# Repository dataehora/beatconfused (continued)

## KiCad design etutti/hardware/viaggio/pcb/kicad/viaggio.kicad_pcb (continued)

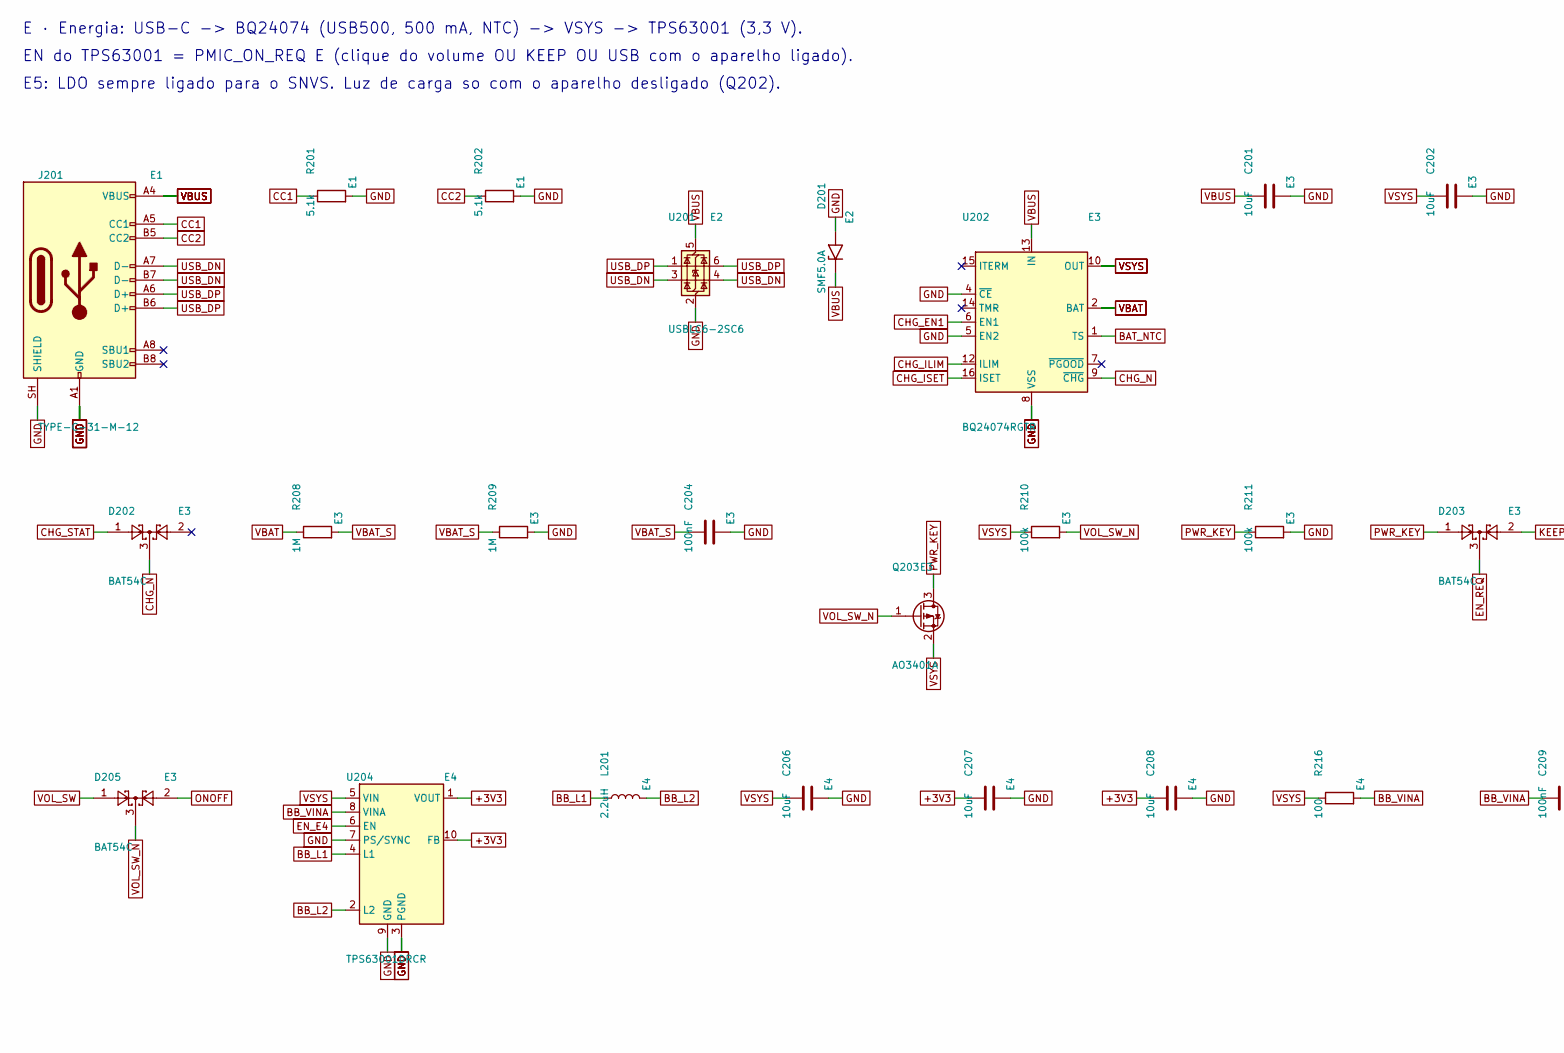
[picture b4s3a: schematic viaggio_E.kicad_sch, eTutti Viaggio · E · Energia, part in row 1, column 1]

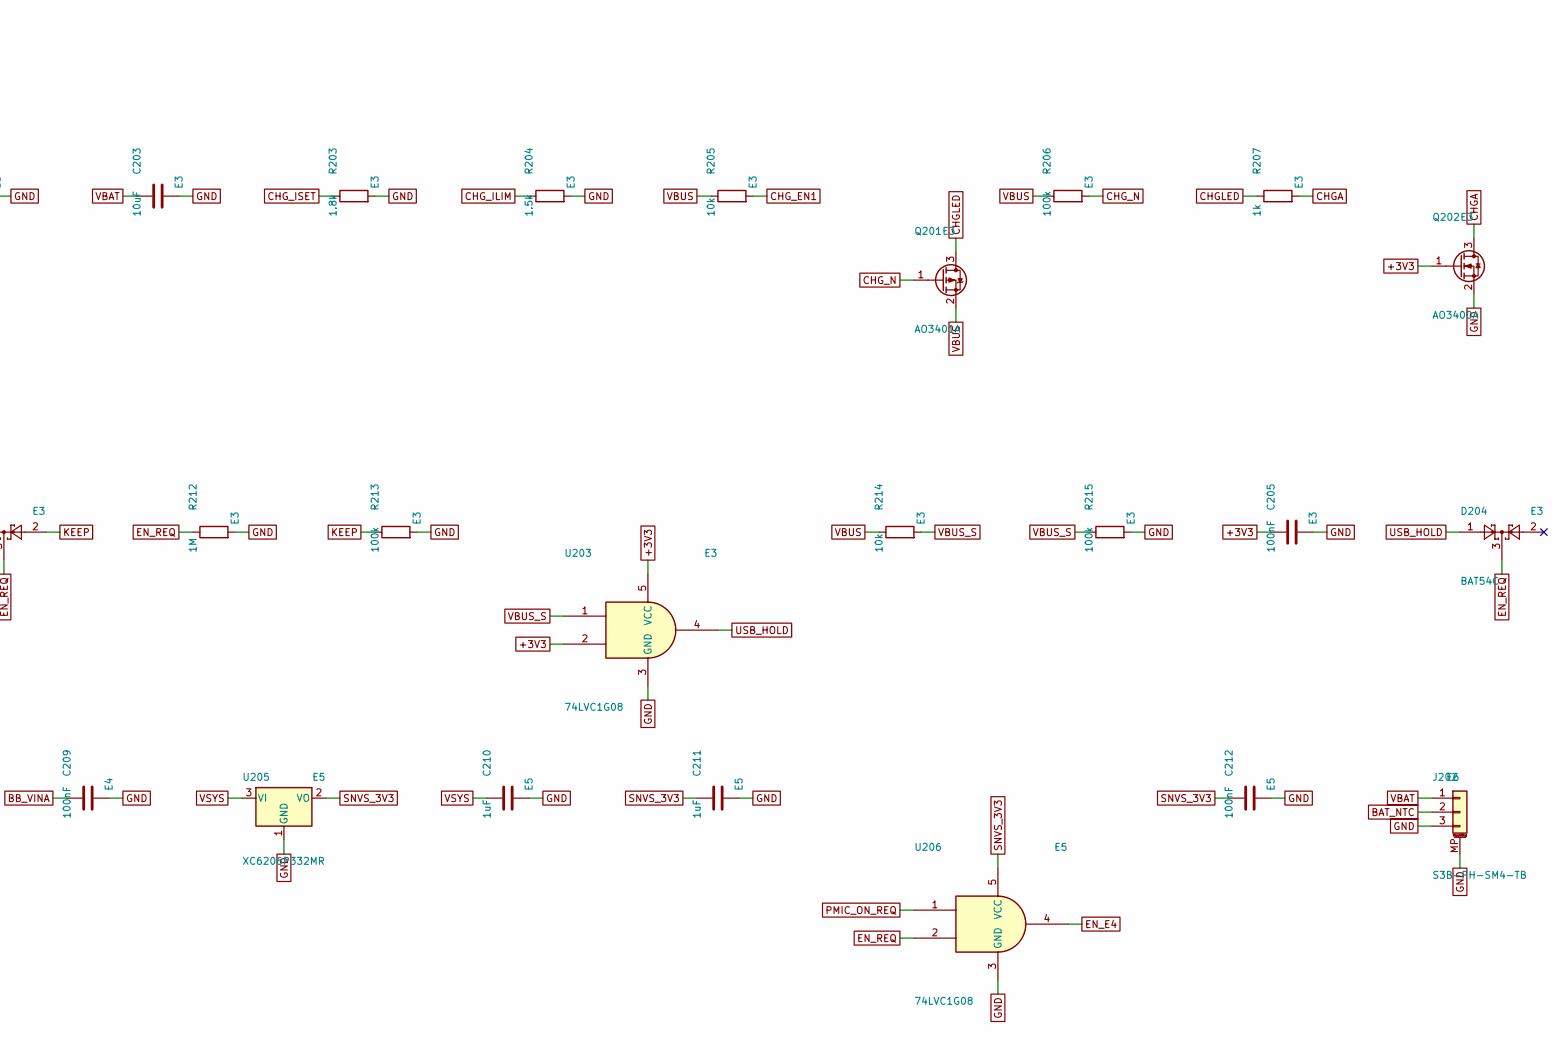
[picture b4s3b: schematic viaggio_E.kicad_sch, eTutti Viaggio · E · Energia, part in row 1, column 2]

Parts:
C201, C202, C203, C206, C207, C208: 10uF; C_0805_2012Metric; LCSC C15850
C204, C205, C209, C212: 100nF; C_0402_1005Metric; LCSC C1525
C210, C211: 1uF; C_0402_1005Metric; LCSC C52923
D201: SMF5.0A; D_SOD-123F; LCSC C151296
D202, D203, D204, D205: BAT54C; SOT-23; LCSC C134405
J201: TYPE-C-31-M-12; USB_C_Receptacle_HRO_TYPE-C-31-M-12; LCSC C165948
J202: S3B-PH-SM4-TB; JST_PH_S3B-PH-SM4-TB_1x03-1MP_P2.00mm_Horizontal; LCSC C265101
L201: 2.2uH; L_Changjiang_FNR4020S; LCSC C167825
Q201, Q203: AO3401A; SOT-23; LCSC C15127
Q202: AO3400A; SOT-23; LCSC C20917
R201, R202: 5.1k; R_0402_1005Metric; LCSC C25905
R203: 1.8k; R_0402_1005Metric; LCSC C25811
R204: 1.5k; R_0402_1005Metric; LCSC C25867
R205, R214: 10k; R_0402_1005Metric; LCSC C25744
R206, R210, R211, R213, R215: 100k; R_0402_1005Metric; LCSC C25741
R207: 1k; R_0402_1005Metric; LCSC C11702
R208, R209, R212: 1M; R_0402_1005Metric; LCSC C26083
R216: 100; R_0402_1005Metric; LCSC C25076
U201: USBLC6-2SC6; SOT-23-6; LCSC C7519
U202: BQ24074RGTR; VQFN-16-1EP_3x3mm_P0.5mm_EP1.6x1.6mm; LCSC C54313
U203, U206: 74LVC1G08; SOT-23-5; LCSC C7666
U204: TPS63001DRCR; Texas_DRC0010J; LCSC C28060
U205: XC6206P332MR; SOT-23-3; LCSC C5446

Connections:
+3V3: C205.1, C207.1, C208.1, Q202.1 (G), U203.2, U203.5 (VCC), U204.1 (VOUT), U204.10 (FB); also elsewhere on the board
BAT_NTC: J202.2, U202.1 (TS)
BB_L1: L201.1, U204.4 (L1)
BB_L2: L201.2, U204.2 (L2)
BB_VINA: C209.1, R216.2, U204.8 (VINA)
CC1: J201.A5 (CC1), R201.1
CC2: J201.B5 (CC2), R202.1
CHGA: Q202.3 (D), R207.2; also elsewhere on the board
CHGLED: Q201.3 (D), R207.1
CHG_EN1: R205.2, U202.6 (EN1)
CHG_ILIM: R204.1, U202.12 (ILIM)
CHG_ISET: R203.1, U202.16 (ISET)
CHG_N: D202.3, Q201.1 (G), R206.2, U202.9 (~CHG)
CHG_STAT: D202.1; also elsewhere on the board
EN_E4: U204.6 (EN), U206.4
EN_REQ: D203.3, D204.3, R212.1, U206.2
GND: C201.2, C202.2, C203.2, C204.2, C205.2, C206.2, C207.2, C208.2, C209.2, C210.2, C211.2, C212.2, D201.2 (A2), J201.A1 (GND), J201.A12 (GND), J201.B1 (GND), J201.B12 (GND), J201.SH (SHIELD), J202.3, J202.MP (MountPin), Q202.2 (S), R201.2, R202.2, R203.2, R204.2, R209.2, R211.2, R212.2, R213.2, R215.2, U201.2 (GND), U202.4 (~CE), U202.5 (EN2), U202.8 (VSS), U202.17 (VSS), U203.3 (GND), U204.3 (PGND), U204.7 (PS/SYNC), U204.9 (GND), U204.11 (PGND), U205.1 (GND), U206.3 (GND); also elsewhere on the board
KEEP: D203.2, R213.1; also elsewhere on the board
ONOFF: D205.2; also elsewhere on the board
PMIC_ON_REQ: U206.1; also elsewhere on the board
PWR_KEY: D203.1, Q203.3 (D), R211.1
SNVS_3V3: C211.1, C212.1, U205.2 (VO), U206.5 (VCC); also elsewhere on the board
USB_DN: J201.A7 (D-), J201.B7 (D-), U201.3 (I/O2), U201.4 (I/O2); also elsewhere on the board
USB_DP: J201.A6 (D+), J201.B6 (D+), U201.1 (I/O1), U201.6 (I/O1); also elsewhere on the board
USB_HOLD: D204.1, U203.4
VBAT: C203.1, J202.1, R208.1, U202.2 (BAT), U202.3 (BAT)
VBAT_S: C204.1, R208.2, R209.1; also elsewhere on the board
VBUS: C201.1, D201.1 (A1), J201.A4 (VBUS), J201.A9 (VBUS), J201.B4 (VBUS), J201.B9 (VBUS), Q201.2 (S), R205.1, R206.1, R214.1, U201.5 (VBUS), U202.13 (IN); also elsewhere on the board
VBUS_S: R214.2, R215.1, U203.1
VOL_SW: D205.1; also elsewhere on the board
VOL_SW_N: D205.3, Q203.1 (G), R210.2; also elsewhere on the board
VSYS: C202.1, C206.1, C210.1, Q203.2 (S), R210.1, R216.1, U202.10 (OUT), U202.11 (OUT), U204.5 (VIN), U205.3 (VI); also elsewhere on the board

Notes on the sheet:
E · Energia: USB-C -> BQ24074 (USB500, 500 mA, NTC) -> VSYS -> TPS63001 (3,3 V).
EN do TPS63001 = PMIC_ON_REQ E (clique do volume OU KEEP OU USB com o aparelho ligado).
E5: LDO sempre ligado para o SNVS. Luz de carga so com o aparelho desligado (Q202).

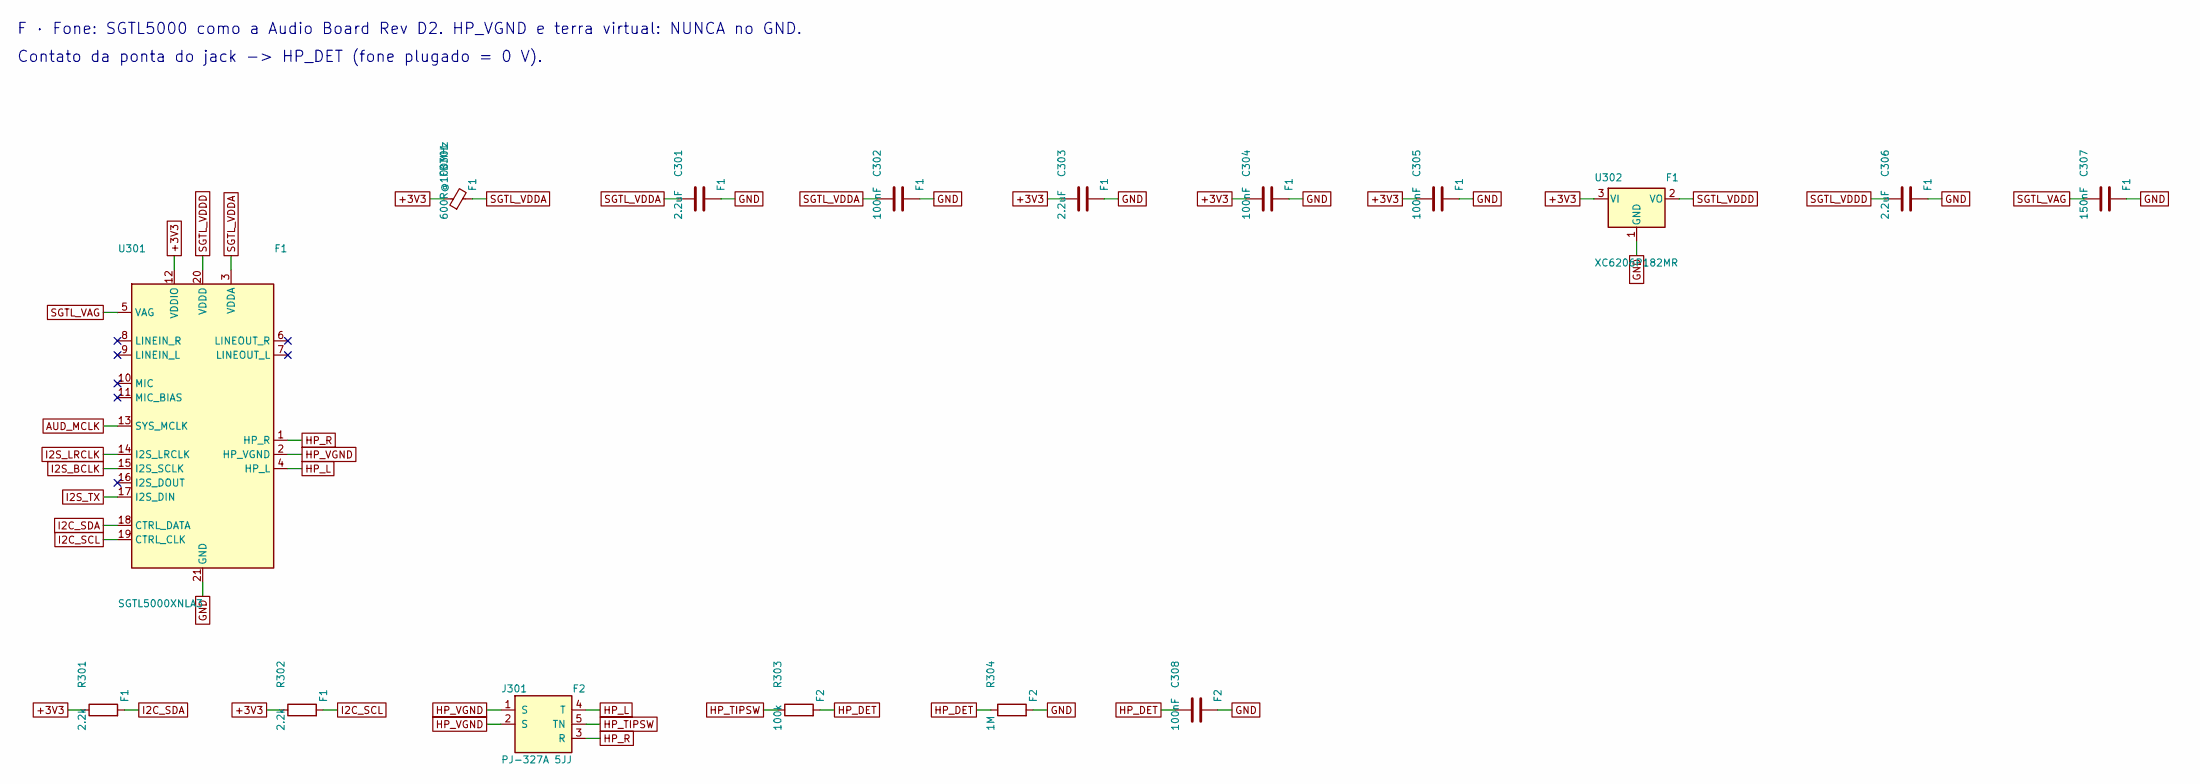
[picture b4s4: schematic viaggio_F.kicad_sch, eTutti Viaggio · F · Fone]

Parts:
C301, C303, C306: 2.2uF; C_0402_1005Metric; LCSC C12530
C302, C304, C305, C308: 100nF; C_0402_1005Metric; LCSC C1525
C307: 150nF; C_0402_1005Metric
FB301: 600R@100MHz; L_0603_1608Metric
J301: PJ-327A 5JJ; Jack_3.5mm_PJ-327A_SMD; LCSC C668605
R301, R302: 2.2k; R_0402_1005Metric; LCSC C25879
R303: 100k; R_0402_1005Metric; LCSC C25741
R304: 1M; R_0402_1005Metric; LCSC C26083
U301: SGTL5000XNLA3; QFN-20-1EP_3x3mm_P0.4mm_EP1.65x1.65mm; LCSC C511764
U302: XC6206P182MR; SOT-23-3; LCSC C347373

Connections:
+3V3: C303.1, C304.1, C305.1, FB301.1, R301.1, R302.1, U301.12 (VDDIO), U302.3 (VI); also elsewhere on the board
AUD_MCLK: U301.13 (SYS_MCLK); also elsewhere on the board
GND: C301.2, C302.2, C303.2, C304.2, C305.2, C306.2, C307.2, C308.2, R304.2, U301.21 (GND), U302.1 (GND); also elsewhere on the board
HP_DET: C308.1, R303.2, R304.1; also elsewhere on the board
HP_L: J301.4 (T), U301.4 (HP_L)
HP_R: J301.3 (R), U301.1 (HP_R)
HP_TIPSW: J301.5 (TN), R303.1
HP_VGND: J301.1 (S), J301.2 (S), U301.2 (HP_VGND)
I2C_SCL: R302.2, U301.19 (CTRL_CLK); also elsewhere on the board
I2C_SDA: R301.2, U301.18 (CTRL_DATA); also elsewhere on the board
I2S_BCLK: U301.15 (I2S_SCLK); also elsewhere on the board
I2S_LRCLK: U301.14 (I2S_LRCLK); also elsewhere on the board
I2S_TX: U301.17 (I2S_DIN); also elsewhere on the board
SGTL_VAG: C307.1, U301.5 (VAG)
SGTL_VDDA: C301.1, C302.1, FB301.2, U301.3 (VDDA)
SGTL_VDDD: C306.1, U301.20 (VDDD), U302.2 (VO)

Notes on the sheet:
F · Fone: SGTL5000 como a Audio Board Rev D2. HP_VGND e terra virtual: NUNCA no GND.
Contato da ponta do jack -> HP_DET (fone plugado = 0 V).

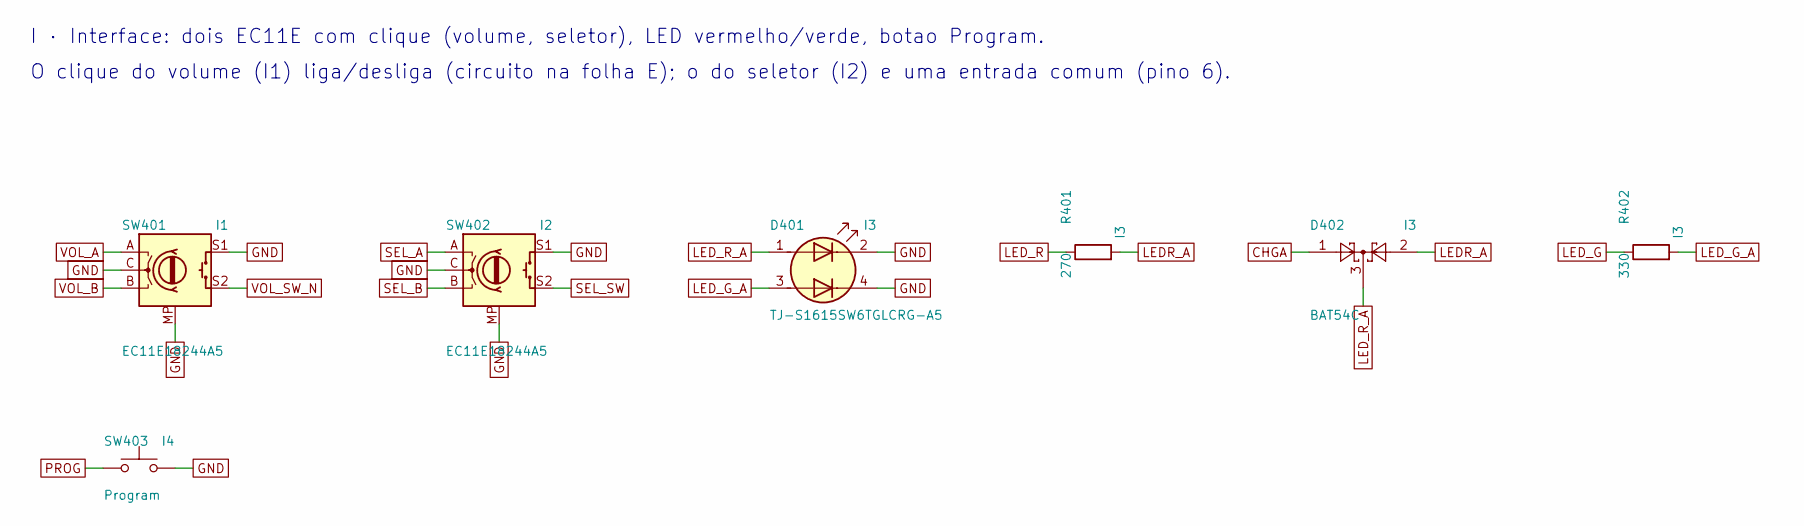
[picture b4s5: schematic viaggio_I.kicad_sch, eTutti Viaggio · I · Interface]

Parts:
D401: TJ-S1615SW6TGLCRG-A5; LED_1615_RG_4pad; LCSC C273605
D402: BAT54C; SOT-23; LCSC C134405
R401: 270; R_0402_1005Metric; LCSC C25190
R402: 330; R_0402_1005Metric; LCSC C25104
SW401, SW402: EC11E18244A5; RotaryEncoder_Alps_EC11E-Switch_Vertical_H20mm; LCSC C255515
SW403: Program; SW_Push_1P1T_XKB_TS-1187A; LCSC C318884

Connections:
CHGA: D402.1; also elsewhere on the board
GND: D401.2 (K1), D401.4 (K2), SW401.C, SW401.MP, SW401.S1, SW402.C, SW402.MP, SW402.S1, SW403.2; also elsewhere on the board
LEDR_A: D402.2, R401.2
LED_G: R402.1; also elsewhere on the board
LED_G_A: D401.3 (A2), R402.2
LED_R: R401.1; also elsewhere on the board
LED_R_A: D401.1 (A1), D402.3
PROG: SW403.1; also elsewhere on the board
SEL_A: SW402.A; also elsewhere on the board
SEL_B: SW402.B; also elsewhere on the board
SEL_SW: SW402.S2; also elsewhere on the board
VOL_A: SW401.A; also elsewhere on the board
VOL_B: SW401.B; also elsewhere on the board
VOL_SW_N: SW401.S2; also elsewhere on the board

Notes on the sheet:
I · Interface: dois EC11E com clique (volume, seletor), LED vermelho/verde, botao Program.
O clique do volume (I1) liga/desliga (circuito na folha E); o do seletor (I2) e uma entrada comum (pino 6).

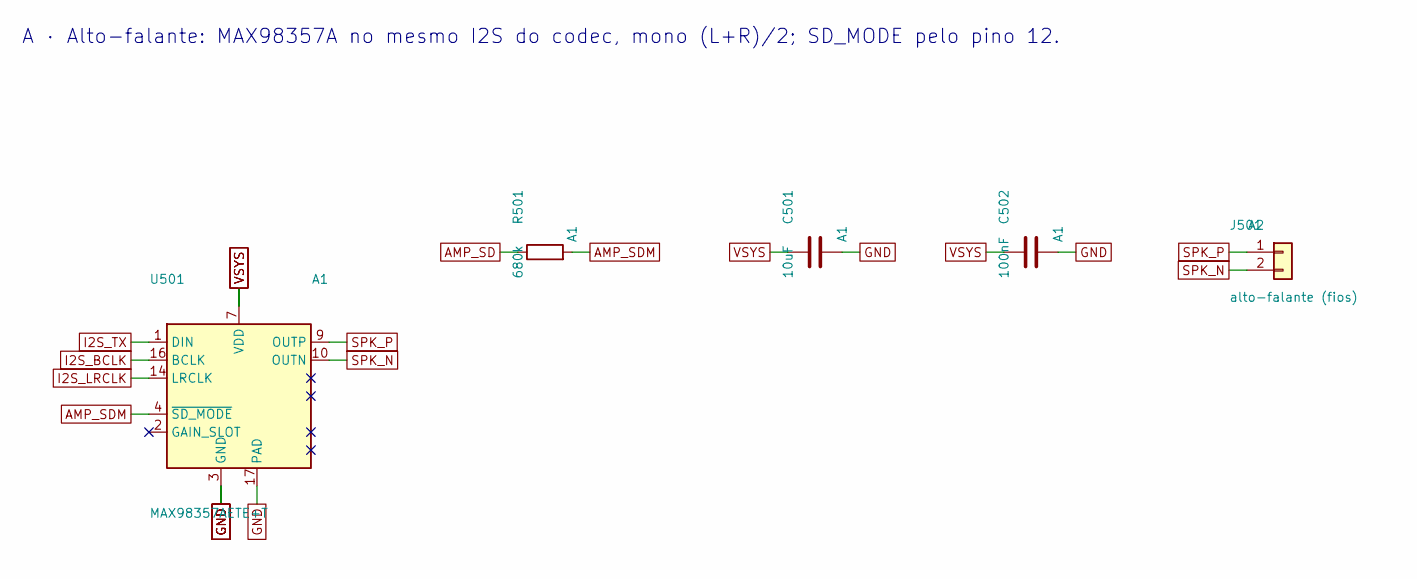
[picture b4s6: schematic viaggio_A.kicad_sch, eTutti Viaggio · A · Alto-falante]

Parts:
C501: 10uF; C_0805_2012Metric; LCSC C15850
C502: 100nF; C_0402_1005Metric; LCSC C1525
J501: alto-falante (fios); SolderWire-0.127sqmm_1x02_P3.7mm_D0.48mm_OD1mm
R501: 680k; R_0402_1005Metric
U501: MAX98357AETE+T; TQFN-16-1EP_3x3mm_P0.5mm_EP1.23x1.23mm; LCSC C910544

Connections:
AMP_SD: R501.1; also elsewhere on the board
AMP_SDM: R501.2, U501.4 (~SD_MODE)
GND: C501.2, C502.2, U501.3 (GND), U501.11 (GND), U501.15 (GND), U501.17 (PAD); also elsewhere on the board
I2S_BCLK: U501.16 (BCLK); also elsewhere on the board
I2S_LRCLK: U501.14 (LRCLK); also elsewhere on the board
I2S_TX: U501.1 (DIN); also elsewhere on the board
SPK_N: J501.2, U501.10 (OUTN)
SPK_P: J501.1, U501.9 (OUTP)
VSYS: C501.1, C502.1, U501.7 (VDD), U501.8 (VDD); also elsewhere on the board

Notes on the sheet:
A · Alto-falante: MAX98357A no mesmo I2S do codec, mono (L+R)/2; SD_MODE pelo pino 12.

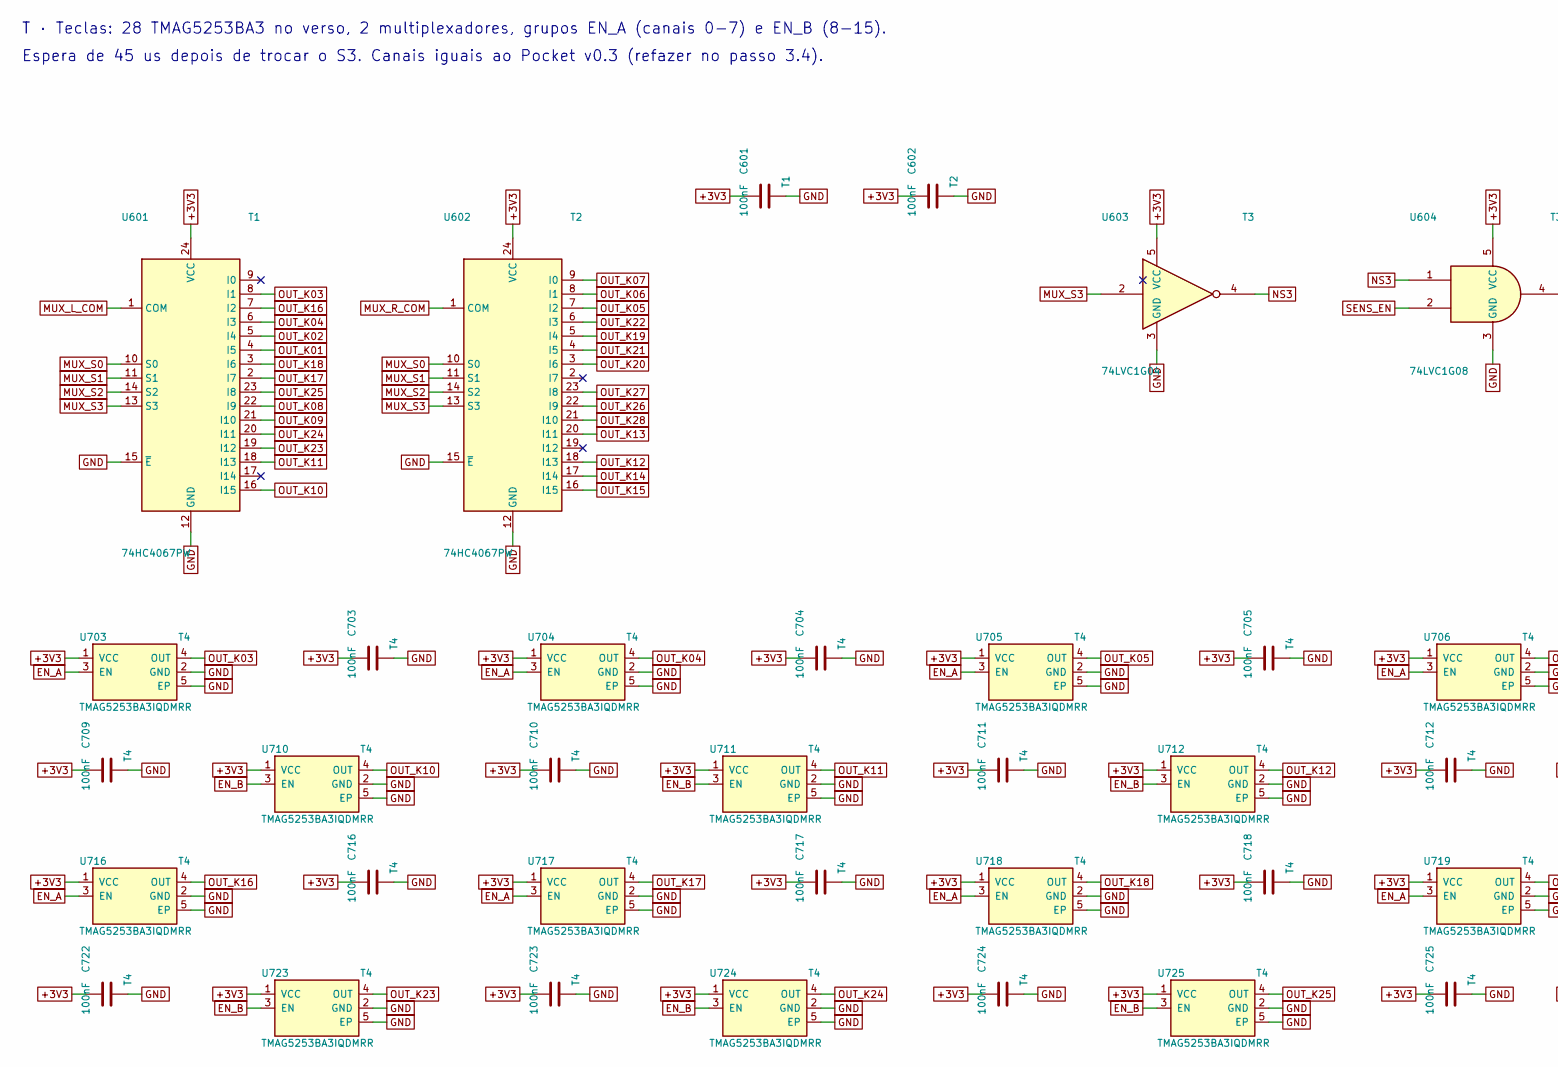
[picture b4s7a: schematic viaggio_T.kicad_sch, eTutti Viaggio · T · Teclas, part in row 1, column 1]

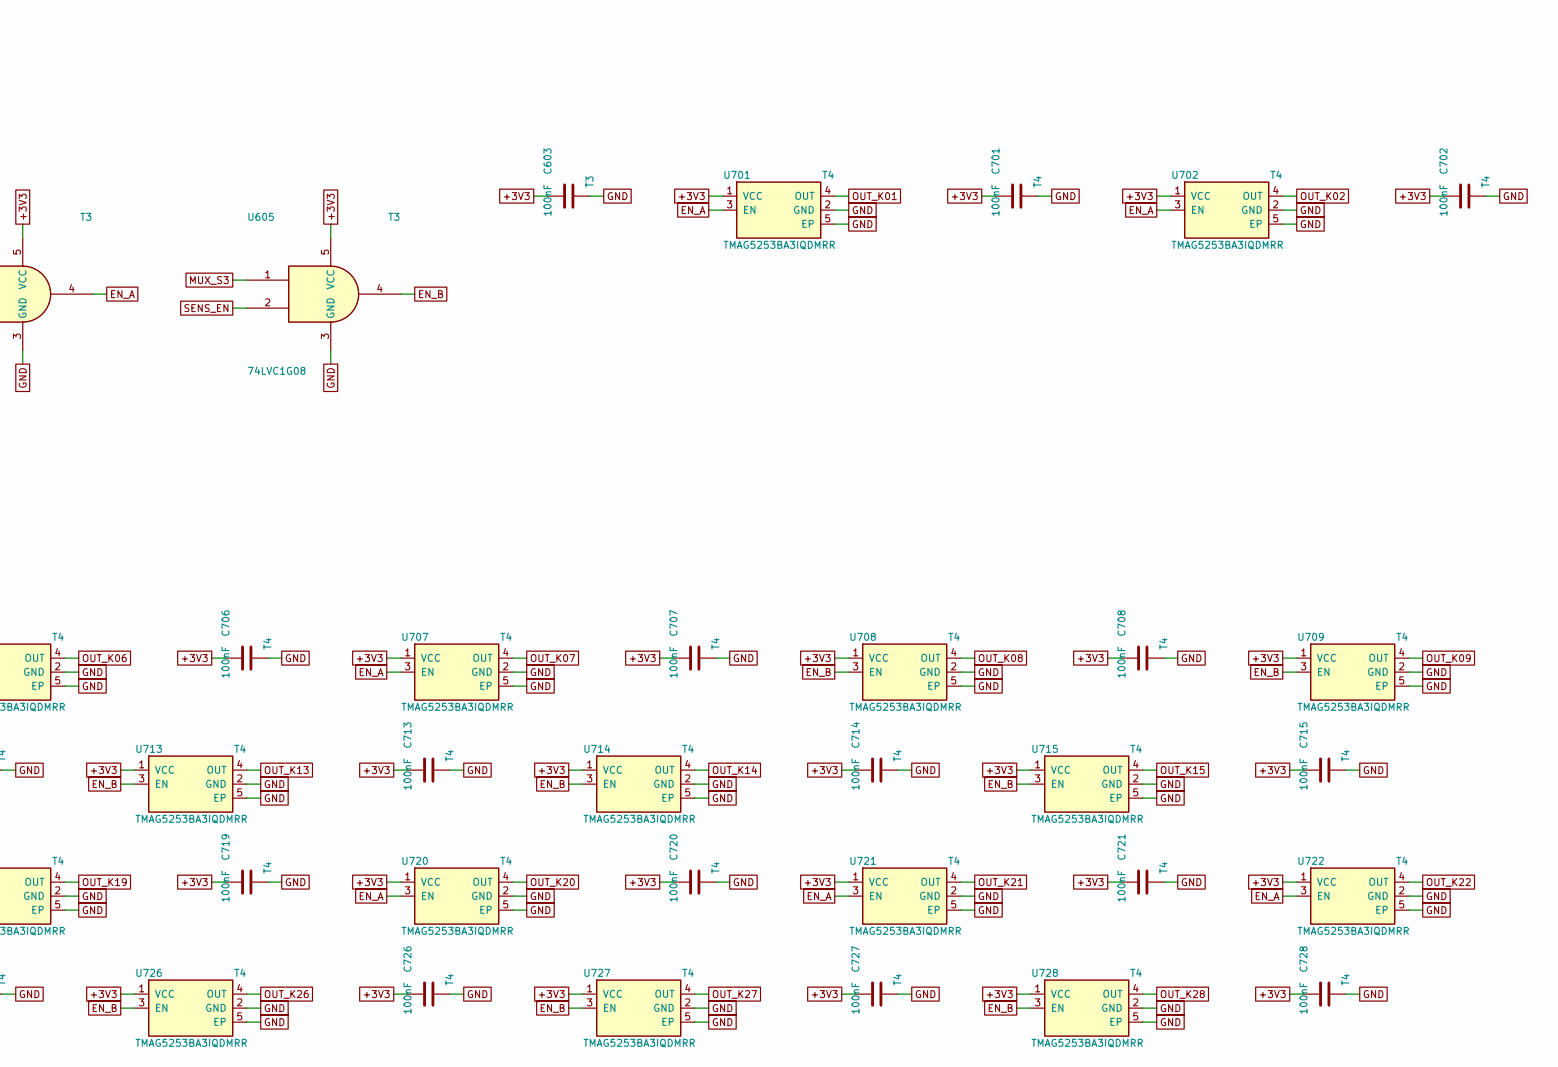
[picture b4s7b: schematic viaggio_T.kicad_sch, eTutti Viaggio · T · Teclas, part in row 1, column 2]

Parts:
C601, C602, C603, C701, C702, C703, C704, C705, C706, C707, C708, C709, C710, C711, C712, C713, C714, C715, C716, C717, C718, C719, C720, C721, C722, C723, C724, C725, C726, C727, C728: 100nF; C_0402_1005Metric; LCSC C1525
U601, U602: 74HC4067PW; TSSOP-24_4.4x7.8mm_P0.65mm; LCSC C547038
U603: 74LVC1G04; SOT-23-5; LCSC C7827
U604, U605: 74LVC1G08; SOT-23-5; LCSC C7666
U701, U702, U703, U704, U705, U706, U707, U708, U709, U710, U711, U712, U713, U714, U715, U716, U717, U718, U719, U720, U721, U722, U723, U724, U725, U726, U727, U728: TMAG5253BA3IQDMRR; Texas_X2SON-4-1EP_1.1x1.4mm_P0.5mm_EP0.8x0.6mm

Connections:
+3V3: C601.1, C602.1, C603.1, C701.1, C702.1, C703.1, C704.1, C705.1, C706.1, C707.1, C708.1, C709.1, C710.1, C711.1, C712.1, C713.1, C714.1, C715.1, C716.1, C717.1, C718.1, C719.1, C720.1, C721.1, C722.1, C723.1, C724.1, C725.1, C726.1, C727.1, C728.1, U601.24 (VCC), U602.24 (VCC), U603.5 (VCC), U604.5 (VCC), U605.5 (VCC), U701.1 (VCC), U702.1 (VCC), U703.1 (VCC), U704.1 (VCC), U705.1 (VCC), U706.1 (VCC), U707.1 (VCC), U708.1 (VCC), U709.1 (VCC), U710.1 (VCC), U711.1 (VCC), U712.1 (VCC), U713.1 (VCC), U714.1 (VCC), U715.1 (VCC), U716.1 (VCC), U717.1 (VCC), U718.1 (VCC), U719.1 (VCC), U720.1 (VCC), U721.1 (VCC), U722.1 (VCC), U723.1 (VCC), U724.1 (VCC), U725.1 (VCC), U726.1 (VCC), U727.1 (VCC), U728.1 (VCC); also elsewhere on the board
EN_A: U604.4, U701.3 (EN), U702.3 (EN), U703.3 (EN), U704.3 (EN), U705.3 (EN), U706.3 (EN), U707.3 (EN), U716.3 (EN), U717.3 (EN), U718.3 (EN), U719.3 (EN), U720.3 (EN), U721.3 (EN), U722.3 (EN)
EN_B: U605.4, U708.3 (EN), U709.3 (EN), U710.3 (EN), U711.3 (EN), U712.3 (EN), U713.3 (EN), U714.3 (EN), U715.3 (EN), U723.3 (EN), U724.3 (EN), U725.3 (EN), U726.3 (EN), U727.3 (EN), U728.3 (EN)
GND: C601.2, C602.2, C603.2, C701.2, C702.2, C703.2, C704.2, C705.2, C706.2, C707.2, C708.2, C709.2, C710.2, C711.2, C712.2, C713.2, C714.2, C715.2, C716.2, C717.2, C718.2, C719.2, C720.2, C721.2, C722.2, C723.2, C724.2, C725.2, C726.2, C727.2, C728.2, U601.12 (GND), U601.15 (~E), U602.12 (GND), U602.15 (~E), U603.3 (GND), U604.3 (GND), U605.3 (GND), U701.2 (GND), U701.5 (EP), U702.2 (GND), U702.5 (EP), U703.2 (GND), U703.5 (EP), U704.2 (GND), U704.5 (EP), U705.2 (GND), U705.5 (EP), U706.2 (GND), U706.5 (EP), U707.2 (GND), U707.5 (EP), U708.2 (GND), U708.5 (EP), U709.2 (GND), U709.5 (EP), U710.2 (GND), U710.5 (EP), U711.2 (GND), U711.5 (EP), U712.2 (GND), U712.5 (EP), U713.2 (GND), U713.5 (EP), U714.2 (GND), U714.5 (EP), U715.2 (GND), U715.5 (EP), U716.2 (GND), U716.5 (EP), U717.2 (GND), U717.5 (EP), U718.2 (GND), U718.5 (EP), U719.2 (GND), U719.5 (EP), U720.2 (GND), U720.5 (EP), U721.2 (GND), U721.5 (EP), U722.2 (GND), U722.5 (EP), U723.2 (GND), U723.5 (EP), U724.2 (GND), U724.5 (EP), U725.2 (GND), U725.5 (EP), U726.2 (GND), U726.5 (EP), U727.2 (GND), U727.5 (EP), U728.2 (GND), U728.5 (EP); also elsewhere on the board
MUX_L_COM: U601.1 (COM); also elsewhere on the board
MUX_R_COM: U602.1 (COM); also elsewhere on the board
MUX_S0: U601.10 (S0), U602.10 (S0); also elsewhere on the board
MUX_S1: U601.11 (S1), U602.11 (S1); also elsewhere on the board
MUX_S2: U601.14 (S2), U602.14 (S2); also elsewhere on the board
MUX_S3: U601.13 (S3), U602.13 (S3), U603.2, U605.1; also elsewhere on the board
NS3: U603.4, U604.1
OUT_K01: U601.4 (I5), U701.4 (OUT)
OUT_K02: U601.5 (I4), U702.4 (OUT)
OUT_K03: U601.8 (I1), U703.4 (OUT)
OUT_K04: U601.6 (I3), U704.4 (OUT)
OUT_K05: U602.7 (I2), U705.4 (OUT)
OUT_K06: U602.8 (I1), U706.4 (OUT)
OUT_K07: U602.9 (I0), U707.4 (OUT)
OUT_K08: U601.22 (I9), U708.4 (OUT)
OUT_K09: U601.21 (I10), U709.4 (OUT)
OUT_K10: U601.16 (I15), U710.4 (OUT)
OUT_K11: U601.18 (I13), U711.4 (OUT)
OUT_K12: U602.18 (I13), U712.4 (OUT)
OUT_K13: U602.20 (I11), U713.4 (OUT)
OUT_K14: U602.17 (I14), U714.4 (OUT)
OUT_K15: U602.16 (I15), U715.4 (OUT)
OUT_K16: U601.7 (I2), U716.4 (OUT)
OUT_K17: U601.2 (I7), U717.4 (OUT)
OUT_K18: U601.3 (I6), U718.4 (OUT)
OUT_K19: U602.5 (I4), U719.4 (OUT)
OUT_K20: U602.3 (I6), U720.4 (OUT)
OUT_K21: U602.4 (I5), U721.4 (OUT)
OUT_K22: U602.6 (I3), U722.4 (OUT)
OUT_K23: U601.19 (I12), U723.4 (OUT)
OUT_K24: U601.20 (I11), U724.4 (OUT)
OUT_K25: U601.23 (I8), U725.4 (OUT)
OUT_K26: U602.22 (I9), U726.4 (OUT)
OUT_K27: U602.23 (I8), U727.4 (OUT)
OUT_K28: U602.21 (I10), U728.4 (OUT)
SENS_EN: U604.2, U605.2; also elsewhere on the board

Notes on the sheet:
T · Teclas: 28 TMAG5253BA3 no verso, 2 multiplexadores, grupos EN_A (canais 0-7) e EN_B (8-15).
Espera de 45 us depois de trocar o S3. Canais iguais ao Pocket v0.3 (refazer no passo 3.4).

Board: 4 copper layers, 215 parts (156 on the bottom side), 136 nets, no tracks yet.

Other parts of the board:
H1, H2, H3, H4, H5, H6, H7, H8: MountingHole_2.2mm_M2
SW1, SW2, SW3, SW4, SW5, SW6, SW7, SW8, SW9, SW10, SW11, SW12, SW13, SW14, SW15, SW16, SW17, SW18, SW19, SW20, SW21, SW22, SW23, SW24, SW25, SW26, SW27, SW28: Gateron_Magnetic_MX_1u

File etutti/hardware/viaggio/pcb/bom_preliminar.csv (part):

codigo,referencias,qtd,valor_peca,encapsulamento,lcsc,classe_jlc,preco_unit_usd_est,montagem,status,nota
P1,R105,1,100,R_0402_1005Metric,C25076,basica,0.001,JLC,final,"MCLK 11,3 MHz: em serie, junto do P1 (SPEC 4, 8o)"
P1,R101,1,100k,R_0402_1005Metric,C25741,basica,0.001,JLC,final,Teensy R7
P1,C107 C111,2,10nF,C_0402_1005Metric,C15195,basica,0.001,JLC,final,Teensy C5
P1,C101 C104,2,10uF,C_0603_1608Metric,C19702,basica,0.005,JLC,final,Teensy C32
P1,C117,1,10uF,C_0402_1005Metric,C15525,basica,0.004,JLC,conferir,Teensy C31 (0402: cabe sobre o BGA)
P1,L101,1,120R@100MHz,L_0603_1608Metric,-,basica,0.005,JLC,conferir,Teensy L3; >=1 A
P1,C108,1,2.2uF,C_0402_1005Metric,C12530,basica,0.003,JLC,conferir,Teensy C28 (NVCC)
P1,C103 C106 C110 C113 C115 C116 C118 C119,8,220nF,C_0402_1005Metric,C16772,basica,0.002,JLC,conferir,Teensy C19
P1,C102 C105,2,4.7uF,C_0603_1608Metric,C19666,basica,0.004,JLC,final,Teensy C24
P1,C109 C112 C114,3,4.7uF,C_0402_1005Metric,C23733,basica,0.003,JLC,conferir,Teensy C23 (0402: cabe sobre o BGA)
P1,L102,1,4.7uH,L_0805_2012Metric,-,estendida,0.050,JLC,conferir,"Teensy L1; corrente do nucleo (conferir >= 0,5 A)"
P1,D101 D102,2,BAT54C,SOT-23,C134405,estendida,0.020,JLC,final,Teensy D2: o anodo da pilha (VBAT) vai no SNVS_3V3 de E5
P1,U101,1,MIMXRT1062DVJ6B,BGA-196_12x12mm_P0.8mm_RT1062,-,-,11.000,consignada (PJRC ou DigiKey),conferir,"BGA-196 12x12 P0.8 (footprint proprio, figura 54 da NXP); bolas livres sem ligacao (SD_B1_05/N3 e EMC_23/G2 de proposito)"
P2,R104,1,100k,R_0402_1005Metric,C25741,basica,0.001,JLC,final,Teensy R6
P2,C124,1,220nF,C_0402_1005Metric,C16772,basica,0.002,JLC,conferir,Teensy C8
P2,R103,1,470,R_0402_1005Metric,C25117,basica,0.001,JLC,conferir,Teensy R2
P2,U102,1,PJRC MKL02 bootloader (Teensy 4.1),QFN-16-1EP_3x3mm_P0.5mm_EP1.9x1.9mm,-,-,6.000,consignada (PJRC),conferir,"PTA3 -> DCDC_PSWITCH, PTB5 -> AD_B0_08 (pagina da PJRC)"
P2,D103,1,vermelho,LED_0603_1608Metric,C2286,basica,0.010,JLC,conferir,"Teensy D4: LED de erro do bootloader (piscadas da pagina da PJRC), no verso"
P3,C125,1,220nF,C_0402_1005Metric,C16772,basica,0.002,JLC,conferir,desacoplamento (o esquema da PJRC nao mostra o do U3)
P3,U103,1,W25Q64JVSSIM,SOIC-8_5.3x5.3mm_P1.27mm,C5362615,estendida,2.970,JLC,final,64 Mbit = modelo Teensy 4.1; '-M' (SPEC v2.1) serve em qualquer versao do bootloader; LCSC 11656 em estoque (24/10/2026)
P4,C126,1,220nF,C_0402_1005Metric,C16772,basica,0.002,nao montar,conferir,Teensy C21; nao montar
P4,U104,1,APS6404L-3SQR-ZR,Winbond_USON-8-1EP_3x2mm_P0.5mm_EP0.2x1.6mm,C3040877,estendida,1.900,nao montar,conferir,so o lugar (modelos futuros); sem estoque na LCSC em out/2026
P5,C120 C121,2,12pF,C_0402_1005Metric,C1547,basica,0.001,JLC,conferir,Teensy C1
P5,R102,1,2.2M,R_0402_1005Metric,-,estendida,0.002,JLC,conferir,"Teensy R5 (em paralelo com C2, como no esquema da PJRC)"
P5,C122 C123,2,20pF,C_0402_1005Metric,C1554,basica,0.001,JLC,conferir,Teensy C3
P5,Y101,1,24MHz,Crystal_SMD_3225-4Pin_3.2x2.5mm,C431156,estendida,0.100,JLC,conferir,Teensy Y1; 8 pF de carga com 12 pF + ~3 pF de placa (conferir)
P5,Y102,1,32.768kHz,Crystal_SMD_3215-2Pin_3.2x1.5mm,C32346,basica,0.080,JLC,conferir,"Teensy Y2; FC-135 12,5 pF, 3215 (a SPEC pedia 2012: conferir)"
E1,R201 R202,2,5.1k,R_0402_1005Metric,C25905,basica,0.001,JLC,final,
E1,J201,1,TYPE-C-31-M-12,USB_C_Receptacle_HRO_TYPE-C-31-M-12,C165948,estendida,0.150,JLC,final,"lado de cima, borda esquerda, boca para fora"
E2,D201,1,SMF5.0A,D_SOD-123F,C151296,estendida,0.050,JLC,final,TVS do VBUS (Pocket D60)
E2,U201,1,USBLC6-2SC6,SOT-23-6,C7519,basica,0.050,JLC,conferir,
E3,R204,1,1.5k,R_0402_1005Metric,C25867,basica,0.001,JLC,conferir,"so vale com EN2=1 (1,07 A); obrigatorio"
E3,R203,1,1.8k,R_0402_1005Metric,C25811,basica,0.001,JLC,conferir,"ICHG = 890/1800 = 0,49 A"
E3,R206 R210 R211 R213 R215,5,100k,R_0402_1005Metric,C25741,basica,0.001,JLC,final,
E3,C204 C205,2,100nF,C_0402_1005Metric,C1525,basica,0.001,JLC,final,
E3,R205 R214,2,10k,R_0402_1005Metric,C25744,basica,0.001,JLC,final,
E3,C201 C202 C203,3,10uF,C_0805_2012Metric,C15850,basica,0.008,JLC,final,
E3,R208 R209 R212,3,1M,R_0402_1005Metric,C26083,basica,0.001,JLC,final,medida da bateria: V(pino 16) = VBAT/2
E3,R207,1,1k,R_0402_1005Metric,C11702,basica,0.001,JLC,final,
E3,U203,1,74LVC1G08,SOT-23-5,C7666,estendida,0.030,JLC,final,USB_HOLD = USB presente E aparelho ligado (alimentado pelo 3V3)
E3,Q202,1,AO3400A,SOT-23,C20917,basica,0.010,JLC,final,"ligado, a luz de carga apaga (Pocket Q31)"
E3,Q201 Q203,2,AO3401A,SOT-23,C15127,basica,0.010,JLC,final,luz de carga (Pocket Q30)
E3,D202 D203 D204 D205,4,BAT54C,SOT-23,C134405,estendida,0.020,JLC,final,leitura do ~CHG pelo pino 26 (so com USB)
E3,U202,1,BQ24074RGTR,VQFN-16-1EP_3x3mm_P0.5mm_EP1.6x1.6mm,C54313,estendida,1.100,JLC,final,"USB500 (EN2=0, EN1=1), 500 mA, NTC no TS; TMR e ITERM abertos = padrao; OUT 4,4 V com USB"
E4,R216,1,100,R_0402_1005Metric,C25076,basica,0.001,JLC,final,
E4,C209,1,100nF,C_0402_1005Metric,C1525,basica,0.001,JLC,final,
E4,C206 C207 C208,3,10uF,C_0805_2012Metric,C15850,basica,0.008,JLC,final,
E4,L201,1,2.2uH,L_Changjiang_FNR4020S,C167825,estendida,0.080,JLC,final,FNR4020S2R2MT (Pocket L10)
E4,U204,1,TPS63001DRCR,Texas_DRC0010J,C28060,estendida,1.400,JLC,final,"3,3 V fixo; PS/SYNC baixo = economia"
E5,C212,1,100nF,C_0402_1005Metric,C1525,basica,0.001,JLC,final,
E5,C210 C211,2,1uF,C_0402_1005Metric,C52923,basica,0.002,JLC,final,
E5,U206,1,74LVC1G08,SOT-23-5,C7666,estendida,0.030,JLC,final,"EN de E4 = PMIC_ON_REQ E (clique OU KEEP OU USB_HOLD): 3,3 V so depois do SNVS"
E5,U205,1,XC6206P332MR,SOT-23-3,C5446,basica,0.020,JLC,conferir,sempre ligado (1 uA): alimenta o SNVS antes de tudo e a porta U206
E6,J202,1,S3B-PH-SM4-TB,JST_PH_S3B-PH-SM4-TB_1x03-1MP_P2.00mm_Horizontal,C265101,estendida,0.300,JLC,final,"bateria 1 = +, 2 = NTC, 3 = - (ordem do Pocket; conferir o cabo)"
F1,C302 C304 C305,3,100nF,C_0402_1005Metric,C1525,basica,0.001,JLC,final,
F1,C307,1,150nF,C_0402_1005Metric,-,estendida,0.003,JLC,conferir,"Audio Board: 0,15 uF"
F1,R301 R302,2,2.2k,R_0402_1005Metric,C25879,basica,0.001,JLC,conferir,
F1,C301 C303 C306,3,2.2uF,C_0402_1005Metric,C12530,basica,0.003,JLC,conferir,
F1,FB301,1,600R@100MHz,L_0603_1608Metric,-,basica,0.005,JLC,conferir,Audio Board: Ferrite 600 no VDDA
F1,U301,1,SGTL5000XNLA3,QFN-20-1EP_3x3mm_P0.4mm_EP1.65x1.65mm,C511764,estendida,1.800,JLC,conferir,como a Audio Board Rev D2 (endereco I2C fixo 0x0A); sem entrada de linha/microfone
F1,U302,1,XC6206P182MR,SOT-23-3,C347373,estendida,0.030,JLC,conferir,"1,8 V do VDDD (a Audio Board usa AP7313)"
F2,R303,1,100k,R_0402_1005Metric,C25741,basica,0.001,JLC,final,
F2,C308,1,100nF,C_0402_1005Metric,C1525,basica,0.001,JLC,final,
F2,R304,1,1M,R_0402_1005Metric,C26083,basica,0.001,JLC,final,
F2,J301,1,PJ-327A 5JJ,Jack_3.5mm_PJ-327A_SMD,C668605,estendida,0.100,JLC,conferir,"SMD, angulo reto, SHOU HAN; 1/2 manga (HP_VGND, nunca no GND), 3 anel, 4 ponta, 5 contato da ponta (fechado sem plugue)"
I1,SW401,1,EC11E18244A5,RotaryEncoder_Alps_EC11E-Switch_Vertical_H20mm,C255515,estendida,1.200,JLC,final,volume; clique de 2 s liga/desliga; 18 pulsos / 36 detentes (o 15/15 nao tem estoque): ENC_STEPS_PER_DETENT = 2
I2,SW402,1,EC11E18244A5,RotaryEncoder_Alps_EC11E-Switch_Vertical_H20mm,C255515,estendida,1.200,JLC,final,seletor; clique = funcoes de som; 18 pulsos / 36 detentes (o 15/15 nao tem estoque): ENC_STEPS_PER_DETENT = 2
I3,R401,1,270,R_0402_1005Metric,C25190,basica,0.001,JLC,conferir,
I3,R402,1,330,R_0402_1005Metric,C25104,basica,0.001,JLC,conferir,
I3,D402,1,BAT54C,SOT-23,C134405,estendida,0.020,JLC,final,OU do vermelho: luz de carga e firmware (Pocket D30)
I3,D401,1,TJ-S1615SW6TGLCRG-A5,LED_1615_RG_4pad,C273605,estendida,0.020,JLC,final,"1615 vermelho/verde; pads do datasheet: 1 = anodo vermelho, 2 = catodo vermelho, 3 = anodo verde, 4 = catodo verde"
I4,SW403,1,Program,SW_Push_1P1T_XKB_TS-1187A,C318884,basica,0.020,JLC,conferir,"no verso, por um furo no fundo; 5,1 x 5,1 (a SPEC pedia 4 x 4)"
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
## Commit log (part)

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2026-06-17 Add comprehensive README documentation
2026-06-17 Add CNAME for beatconfused.com domain
